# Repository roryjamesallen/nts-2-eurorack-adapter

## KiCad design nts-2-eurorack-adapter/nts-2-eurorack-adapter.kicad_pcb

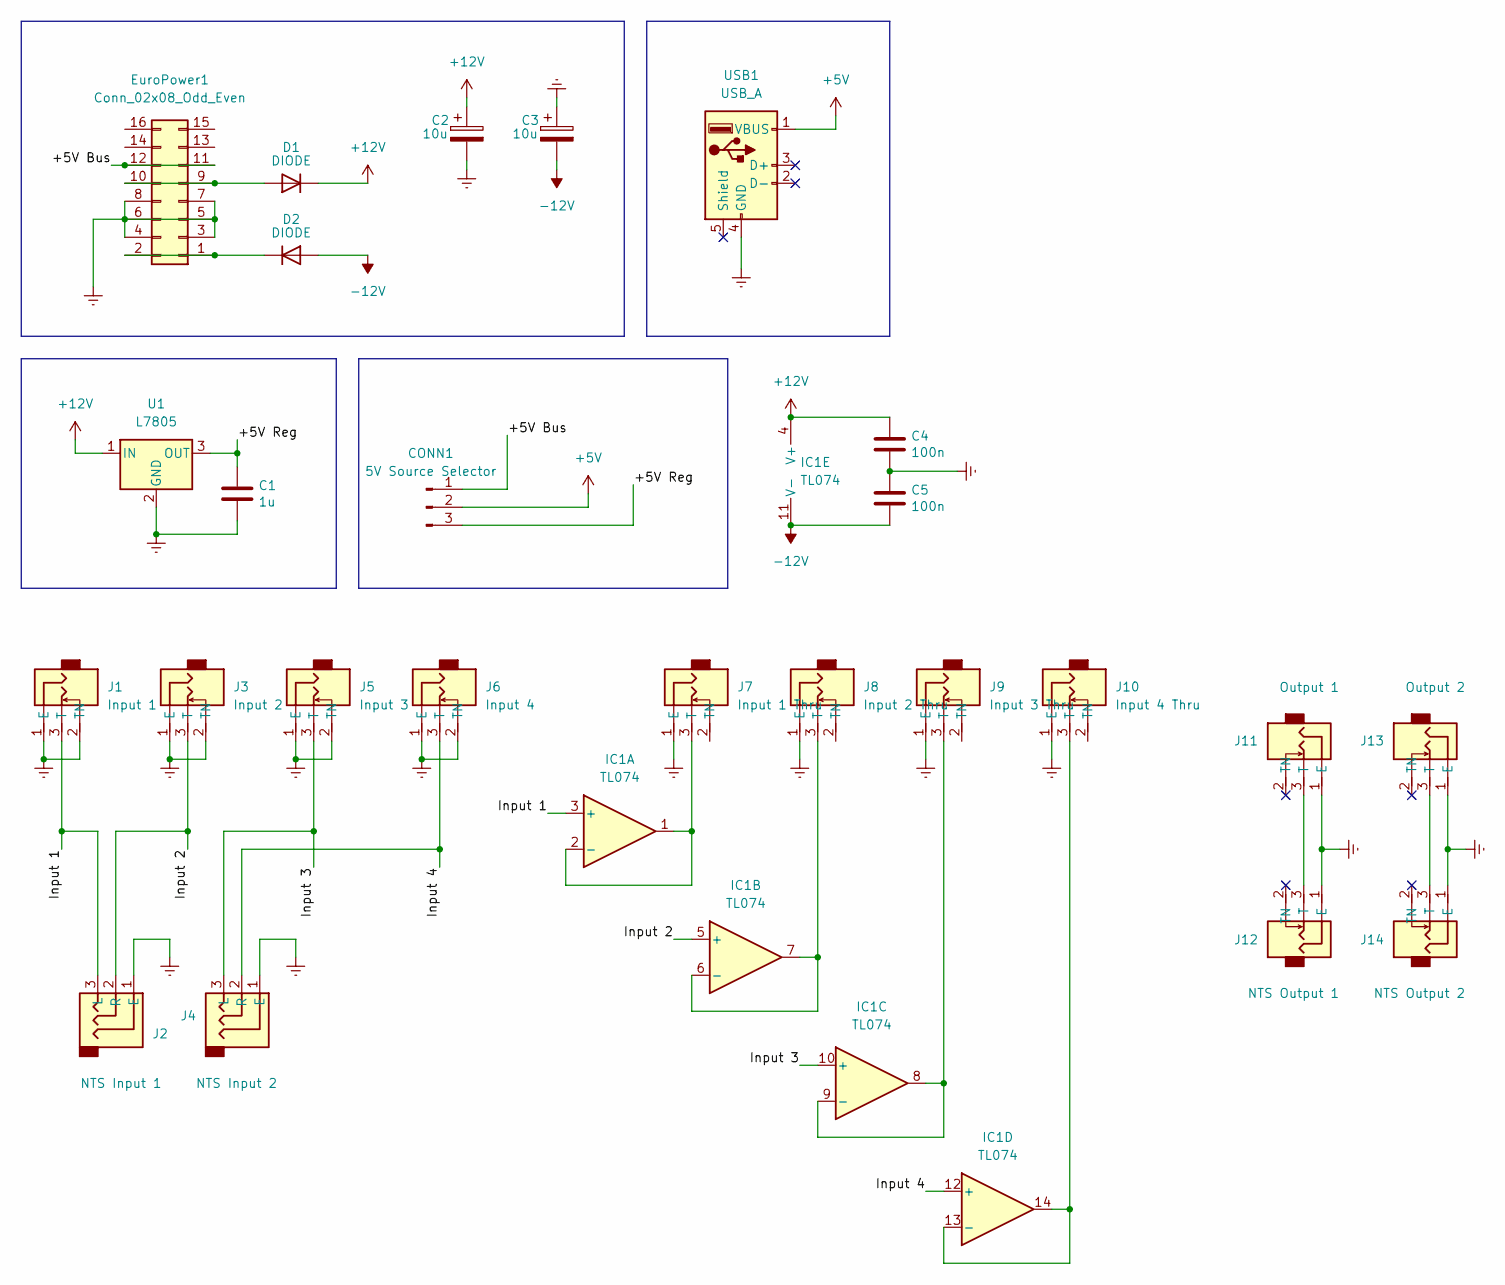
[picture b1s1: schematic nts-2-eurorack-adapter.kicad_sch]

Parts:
C1: 1u; CP_Radial_D5.0mm_P2.50mm
C2, C3: 10u; CP_Radial_D5.0mm_P2.50mm
C4, C5: 100n; CP_Radial_D5.0mm_P2.50mm
CONN1: 5V Source Selector; PinHeader_1x03_P2.54mm_Vertical
D1, D2: DIODE; D_DO-41_SOD81_P7.62mm_Horizontal
EuroPower1: Conn_02x08_Odd_Even; Eurorack Power Header 16 Pin
IC1: TL074; DIP-14 IC Socket
J1: Input 1; Thonkiconn Mono Jack
J2: NTS Input 1; Thonkiconn Stereo Jack
J3: Input 2; Thonkiconn Mono Jack
J4: NTS Input 2; Thonkiconn Stereo Jack
J5: Input 3; Thonkiconn Mono Jack
J6: Input 4; Thonkiconn Mono Jack
J7: Input 1 Thru; Thonkiconn Mono Jack
J8: Input 2 Thru; Thonkiconn Mono Jack
J9: Input 3 Thru; Thonkiconn Mono Jack
J10: Input 4 Thru; Thonkiconn Mono Jack
J11: Output 1; Thonkiconn Mono Jack
J12: NTS Output 1; Thonkiconn Mono Jack
J13: Output 2; Thonkiconn Mono Jack
J14: NTS Output 2; Thonkiconn Mono Jack
U1: L7805; TO-220-3_Horizontal_TabDown
USB1: USB_A; USB_A_Molex_67643_Horizontal

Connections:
+5V: CONN1.2, USB1.1 (VBUS)
+12V: C2.1, C4.1, D1.2 (K), IC1.4 (V+), U1.1 (IN)
-12V: C3.2, C5.2, D2.1 (A), IC1.11 (V-)
/+5V Bus: CONN1.1, EuroPower1.11, EuroPower1.12
/+5V Reg: C1.1, CONN1.3, U1.3 (OUT)
/Input 1: IC1.3 (+), J1.3 (T), J2.3 (L)
/Input 2: IC1.5 (+), J2.2 (R), J3.3 (T)
/Input 3: IC1.10 (+), J4.3 (L), J5.3 (T)
/Input 4: IC1.12 (+), J4.2 (R), J6.3 (T)
Earth: C1.2, C2.2, C3.1, C4.2, C5.1, EuroPower1.3, EuroPower1.4, EuroPower1.5, EuroPower1.6, EuroPower1.7, EuroPower1.8, J1.1 (E), J1.2 (TN), J2.1 (E), J3.1 (E), J3.2 (TN), J4.1 (E), J5.1 (E), J5.2 (TN), J6.1 (E), J6.2 (TN), J7.1 (E), J8.1 (E), J9.1 (E), J10.1 (E), J11.1 (E), J12.1 (E), J13.1 (E), J14.1 (E), U1.2 (GND), USB1.4 (GND)
unnamed: D1.1 (A), EuroPower1.9, EuroPower1.10
unnamed: D2.2 (K), EuroPower1.1, EuroPower1.2
unnamed: IC1.1, IC1.2 (-), J7.3 (T)
unnamed: IC1.6 (-), IC1.7, J8.3 (T)
unnamed: IC1.8, IC1.9 (-), J9.3 (T)
unnamed: IC1.13 (-), IC1.14, J10.3 (T)
unnamed: J11.3 (T), J12.3 (T)
unnamed: J13.3 (T), J14.3 (T)

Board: 2 copper layers, 26 parts (10 on the bottom side), 18 nets, no tracks yet.

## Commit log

2022-05-10 add images and layout
2022-05-11 kicad changes
